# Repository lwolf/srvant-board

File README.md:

# srvant-board

| :warning: WARNING          |
|:---------------------------|
| This is a work-in-progress. No final board have been produced yet. Any part of the schematic and/or PCB could be wrong.|

Design of the carrier board for the Raspberry Pi CM4. The main distinction from existing boards is the presence of the 
BMC (Baseboard Management Controller) which supposed to monitor and control the HOST, allowing the board to act as a real "server".

## Highlevel design / idea:

BMC using lots of GPIO controls the HOST: power cycle, terminal access, switches USB into OTG for flushing.

* CM4 (HOST) features:
  * 1Gb/s ethernet
  * HDMI
  * 1 USB
  * PCIe exposed as M.2 socket to connect nvme drive
  * TPM2.0 (OPTIGA™ TPM SLB 9670)
  * RTC with battery
* BMC features:
  * Always ON
  * 1Gb/s management port
  * USB port for debug
  * USB connection to the HOST for flushing
  * I2C connection to the HOST for additional metrics
  * TTY connection to HOST for SOL (Serial over LAN)
  * measures Current/Power of the board
  * measures Temperature of the board
  * controls FAN (not available in the PoC)

BMC is based on the Allwinner T113 S3 SoM [link to aliexpress](https://www.aliexpress.com/item/1005005389129193.html).

### Power

THere are separate 5v rails for host and BMC. The host one is based on AP64501SP (5V 5A), while BMC is based on AP63205WU (5V 2A).
BMC is always on. Host is being powered either by a signal from BMC or by shortening a jumper.

Main power goes through the shunt resistor connected to the power sensor (INA219A). The value is available to BMC using i2c bus.

### Connectors

#### HOST
Host has a following connectors:
* Ethernet
* HDMI
* USB
* M.2 socket M for nvme disk

#### BMC
BMC has a following connectors:
* Ethernet (1GB/s)
* MicroUSB (debug)

### USB

There is a connection between BMC and HOST using USB to allow flushing the HOST remotely.
Since CM4 has only a single usb line, it is connected to the MUX (FSUSB42MUX) 
in a similar way it is done in the CM4IO board, but instead of switching client mode to microUSB, it goes to BMC.

### RTC

RTC is based on PCF85063AT chip. There are two of them, one for each CPU.
Even though t133-s3 has on-board RTC, it is not exposed from the SOM and reference schematic uses external one.
Both chips are powered by 3.3v coming from BMC and coin cell battery.

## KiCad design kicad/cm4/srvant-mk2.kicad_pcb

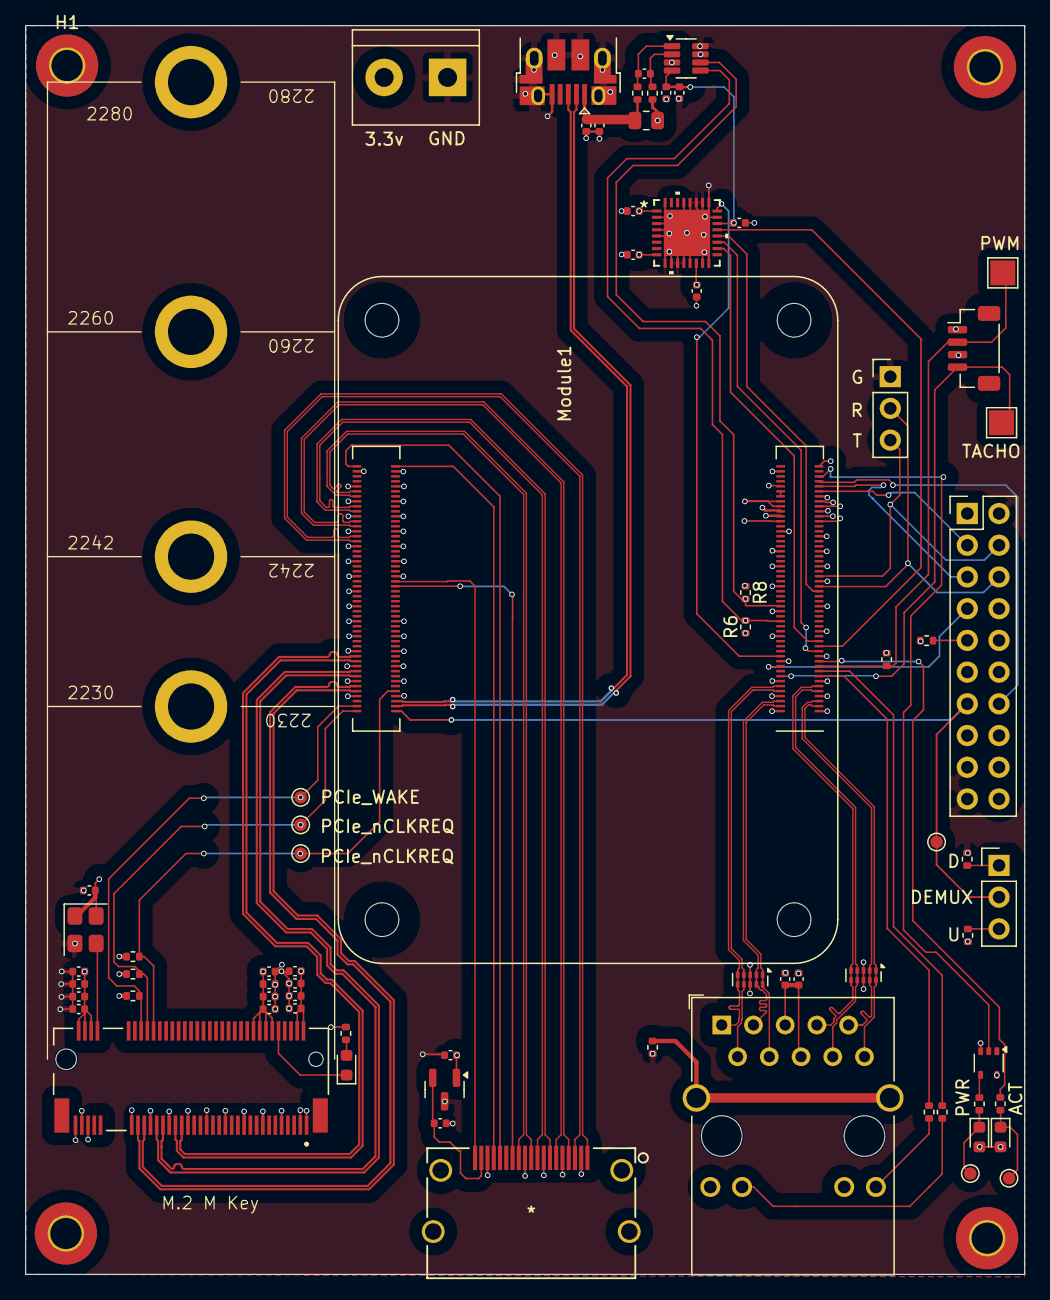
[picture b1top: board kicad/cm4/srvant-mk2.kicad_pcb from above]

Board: 6 copper layers, 80.0 x 100.0 mm, 76 parts (0 on the bottom side), 77 nets.

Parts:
C1, C2: 10uF; C_0402_1005Metric
C3, C5, C23, C25, C29, C30, C31, C42, C43, C44, C49, C50, C51: 100n; C_0402_1005Metric
C4, C35, C36, C37: 10u; C_0402_1005Metric
C28, C38, C39, C40: 1u; C_0402_1005Metric
C46, C47, C48: 1n; C_0402_1005Metric
D1: LED Green; LED_0603_1608Metric
D2: LED Red; LED_0603_1608Metric
D3: LED; LED_0603_1608Metric
FB1: 220R; R_0402_1005Metric
H1, H2, H3, H4: MountingHole; MountingHole_2.5mm_Pad_TopOnly
J1: Screw_Terminal_01x02; TerminalBlock_bornier-2_P5.08mm
J2: USB_B_Micro; USB_Micro-B_Amphenol_10103594-0001LF_Horizontal
J5, J6: Conn_01x03; PinHeader_1x03_P2.54mm_Vertical
J7: ARJM11; RJ45_Wuerth_7499111446_Horizontal
J8: Bus_M.2_Socket_M; M.2 M Key socket_rpi
J9: Conn_02x10_Odd_Even; PinHeader_2x10_P2.54mm_Vertical
J10: HDMI connector; HDMI-10029449-001RLF
J14: JST_SHBM04B-SRSS-TB; JST_SH_BM04B-SRSS-TB_1x04-1MP_P1.00mm_Vertical
Module1: ComputeModule5-CM5; Raspberry-Pi-4-Compute-Module
R1: 0.005R; R_0805_2012Metric
R2, R3: 10R; R_0402_1005Metric
R4: 1k; R_0402_1005Metric
R5, R6, R7, R8, R17, R18, R19, R20: 10K; R_0402_1005Metric
R13, R14: 470R; R_0402_1005Metric
R16: 1K; R_0402_1005Metric
R21: 330R; R_0402_1005Metric
R22: 10K 1%; R_0402_1005Metric
TP1, TP3: TestPoint; TestPoint_Pad_D1.0mm
TP4, TP11: PCIe_nCLKREQ; TestPoint_Pad_D1.0mm
TP5, TP8: PCIe_nRST; TestPoint_Pad_D1.0mm
TP9, TP10: TestPoint; TestPoint_Pad_2.0x2.0mm
U1: INA219AxDCN; SOT-23-8
U4, U5: TPD4EUSB30; USON-10_2.5x1.0mm_P0.5mm
U6: SLB9670VQ20FW785XTMA1; QFN32_SLB9670VQ20FW785XTMA1_INF
U8: 74LVC1G07SE-7; SOT-353_SC-70-5
U9: RT9742SNGV; SOT-23
U10: ASEK-32.768KHZ-L-R-T; Crystal_SMD_3225-4Pin_3.2x2.5mm

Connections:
/+1.8v: Module1.88 (+1.8v_(Output)), Module1.90 (+1.8v_(Output))
/+3.3v_HOST: C4.1, C5.1, C28.1, C29.2, C30.2, C31.2, D1.2 (A), D2.2 (A), J7.11 (LED2+), J7.13 (LED1+), Module1.78 (GPIO_VREF(1.8v/3.3v_Input)), Module1.84 (+3.3v_(Output)), Module1.86 (+3.3v_(Output)), R5.2, R6.1, R8.1, R20.2, R22.1, U1.4 (VS), U6.1 (NCI/VDD), U6.8 (VDD), U6.14 (NCI/VDD), U6.22 (VDD), U8.5 (VCC)
/+3v3_AUX: C35.1, C36.1, C37.1, C38.1, C39.1, C40.1, C42.1, C43.1, C44.1, C46.1, C47.1, C48.1, C51.1, J1.2, J8.2 (3.3V), J8.4 (3.3V), J8.12 (3.3V), J8.14 (3.3V), J8.16 (3.3V), J8.18 (3.3V), J8.70 (3.3V), J8.72 (3.3V), J8.74 (3.3V), R17.2, R18.2, R19.2, R21.1, U10.1 (EN), U10.4 (VDD)
/+5v_HOST: C49.1, J14.1, Module1.77 (+5v_(Input)), Module1.79 (+5v_(Input)), Module1.81 (+5v_(Input)), Module1.83 (+5v_(Input)), Module1.85 (+5v_(Input)), Module1.87 (+5v_(Input)), R1.1, R3.1, U9.1 (IN)
/+5v_HOST_HDMI: C50.1, J10.18 (+5V), U9.2 (OUT)
/+5v_IN: C1.1, C2.1, J2.1 (VBUS), R1.2, R2.1
/BMC_HOST_BT_nDis: J9.5, Module1.91 (BT_nDisable)
/BMC_HOST_EEPROM_nWP: J9.7, Module1.20 (EEPROM_nWP)
/BMC_HOST_I2C_SCK: J9.10, Module1.80 (SCL0)
/BMC_HOST_I2C_SDA: J9.8, Module1.82 (SDA0)
/BMC_HOST_POST_COMPLETE: J9.9, R20.1
/BMC_HOST_POWER_OUT: J9.16, Module1.92 (PWR_BUT)
/BMC_HOST_RESET_OUT: J9.15, Module1.99 (PMIC_ENABLE)
/BMC_HOST_UART_RX: J6.2, J9.6, Module1.51 (GPIO15)
/BMC_HOST_UART_TX: J6.3, J9.4, Module1.55 (GPIO14)
/BMC_HOST_USB_DEMUX_CONTROL: J5.2, J9.13, Module1.101 (USB_OTG_ID), TP8.1
/BMC_HOST_WL_nDis: J9.3, Module1.89 (WiFi_nDisable)
/BMC_HOST_nRPIBOOT: J9.14, Module1.93 (nRPIBOOT)
/ETH_LEDG: Module1.17 (Ethernet_nLED2(3.3v)), R13.2
/ETH_LEDY: Module1.15 (Ethernet_nLED3(3.3v)), R14.2
/GPIO10: J9.20, Module1.44 (GPIO10), R8.2, U1.6 (SDA)
/GPIO11: J9.18, Module1.38 (GPIO11), R6.2, U1.5 (SCL)
/GPIO16: Module1.29 (GPIO16), U6.18 (PIRQ#)
/GPIO18: Module1.49 (GPIO18), U6.20 (CS#)
/GPIO20: Module1.27 (GPIO20), U6.21 (MOSI)
/GPIO21: Module1.25 (GPIO21), U6.19 (SCLK)
/HDMI0_CEC: J10.13 (CEC), Module1.151 (HDMI0_CEC)
/HDMI0_CK_N: J10.12 (CK-), Module1.190 (HDMI0_CLK_N)
/HDMI0_CK_P: J10.10 (CK+), Module1.188 (HDMI0_CLK_P)
/HDMI0_D0_N: J10.9 (D0-), Module1.184 (HDMI0_TX0_N)
/HDMI0_D0_P: J10.7 (D0+), Module1.182 (HDMI0_TX0_P)
/HDMI0_D1_N: J10.6 (D1-), Module1.178 (HDMI0_TX1_N)
/HDMI0_D1_P: J10.4 (D1+), Module1.176 (HDMI0_TX1_P)
/HDMI0_D2_N: J10.3 (D2-), Module1.172 (HDMI0_TX2_N)
/HDMI0_D2_P: J10.1 (D2+), Module1.170 (HDMI0_TX2_P)
/HDMI0_HOTPLUG: J10.19 (HPD/HEAC-), Module1.153 (HDMI0_HOTPLUG)
/HDMI0_SCL: J10.15 (SCL), Module1.200 (HDMI0_SCL)
/HDMI0_SDA: J10.16 (SDA), Module1.199 (HDMI0_SDA)
/HOST_SPI1_MISO: Module1.24 (GPIO26), U6.24 (MISO)
/PCIE_CLK_N: J8.53 (REFCLKn), Module1.112 (PCIe_CLK_N)
/PCIE_CLK_P: J8.55 (REFCLKp), Module1.110 (PCIe_CLK_P)
/PCIE_CLK_nREQ: J8.52 (~CLKREQ), Module1.102 (PCIe_nCLKREQ), R18.1, TP5.1
/PCIE_RX_N: J8.47 (PETn0/SATA-A-), Module1.118 (PCIe_RX_N)
/PCIE_RX_P: J8.49 (PETp0/SATA-A+), Module1.116 (PCIe_RX_P)
/PCIE_TX_N: J8.41 (PERn0/SATA-B+), Module1.124 (PCIe_TX_N)
/PCIE_TX_P: J8.43 (PERp0/SATA-B-), Module1.122 (PCIe_TX_P)
/PCIE_WAKE: J8.54 (~PEWAKE), Module1.104 (PCIE_nWAKE), R19.1, TP11.1
/PCIE_nRST: J8.50 (~PERST), Module1.109 (PCIe_nRST), R17.1, TP4.1
/PWM: J14.2, Module1.19 (FAN_PWM), R22.2, TP9.1
/TACHO: J14.4, Module1.16 (FAN_TACHO), TP10.1
/TRD0_N: J7.2 (TD1-), Module1.10 (Ethernet_Pair0_N), U5.4 (D2+), U5.7
/TRD0_P: J7.1 (TD1+), Module1.12 (Ethernet_Pair0_P), U5.5 (D2-), U5.6
/TRD1_N: J7.3 (TD2+), Module1.6 (Ethernet_Pair1_N), U5.2 (D1-), U5.9
/TRD1_P: J7.4 (TD2-), Module1.4 (Ethernet_Pair1_P), U5.1 (D1+), U5.10
/TRD2_N: J7.8 (TD3-), Module1.9 (Ethernet_Pair2_N), U4.4 (D2+), U4.7
/TRD2_P: J7.7 (TD3+), Module1.11 (Ethernet_Pair2_P), U4.5 (D2-), U4.6
/TRD3_N: J7.9 (TD4+), Module1.5 (Ethernet_Pair3_N), U4.2 (D1-), U4.9
/TRD3_P: J7.10 (TD4-), Module1.3 (Ethernet_Pair3_P), U4.1 (D1+), U4.10
/USB2_N: J2.2 (D-), Module1.103 (USB2_N)
/USB2_P: J2.3 (D+), Module1.105 (USB2_P)
/nPWR_LED: Module1.95 (LED_nPWR), U8.2
GND: C1.2, C2.2, C4.2, C5.2, C23.2, C25.2, C28.2, C29.1, C30.1, C31.1, C35.2, C36.2, C37.2, C38.2, C39.2, C40.2, C42.2, C43.2, C44.2, C46.2, C47.2, C48.2, C49.2, C50.2, C51.2, FB1.2, J1.1, J2.5 (GND), J2.6 (Shield), J6.1, J8.1 (GND), J8.3 (GND), J8.9 (GND), J8.15 (GND), J8.21 (GND), J8.27 (GND), J8.33 (GND), J8.39 (GND), J8.45 (GND), J8.51 (GND), J8.57 (GND), J8.71 (GND), J8.73 (GND), J8.75 (GND), J9.2, J9.11, J9.12, J9.17, J9.19, J10.2 (D2S), J10.5 (D1S), J10.8 (D0S), J10.11 (CKS), J10.17 (GND), J14.3, Module1.1 (GND), Module1.2 (GND), Module1.7 (GND), Module1.8 (GND), Module1.13 (GND), Module1.14 (GND), Module1.22 (GND), Module1.23 (GND), Module1.32 (GND), Module1.33 (GND), Module1.42 (GND), Module1.43 (GND), Module1.52 (GND), Module1.53 (GND), Module1.59 (GND), Module1.60 (GND), Module1.65 (GND), Module1.66 (GND), Module1.71 (GND), Module1.74 (GND), Module1.98 (GND), Module1.107 (GND), Module1.108 (GND), Module1.113 (GND), Module1.114 (GND), Module1.119 (GND), Module1.120 (GND), Module1.125 (GND), Module1.126 (GND), Module1.131 (GND), Module1.132 (GND), Module1.137 (GND), Module1.138 (GND), Module1.144 (GND), Module1.150 (GND), Module1.155 (GND), Module1.156 (GND), Module1.161 (GND), Module1.162 (GND), Module1.167 (GND), Module1.168 (GND), Module1.173 (GND), Module1.174 (GND), Module1.179 (GND), Module1.180 (GND), Module1.185 (GND), Module1.186 (GND), Module1.191 (GND), Module1.192 (GND), Module1.197 (GND), Module1.198 (GND), R7.1, U1.3 (GND), U1.7 (A0), U1.8 (A1), U4.3 (GND), U4.8 (GND), U5.3 (GND), U5.8 (GND), U6.2 (GND), U6.3 (NCI), U6.4 (NCI), U6.5 (NCI), U6.9 (GND), U6.10 (NCI), U6.11 (NCI), U6.12 (NCI), U6.13 (NCI), U6.15 (NCI), U6.16 (NCI/GND), U6.23 (GND), U6.25 (NCI), U6.26 (NCI), U6.27 (NCI), U6.28 (NCI), U6.29 (NCI), U6.32 (NCI), U6.33 (GND), U8.3 (GND), U9.3 (GND), U10.2 (GND)
unnamed: C23.1, C25.1, J7.5 (CT), J7.6 (CT)
unnamed: D1.1 (K), R4.1, TP1.1
unnamed: D2.1 (K), R16.1, TP3.1
unnamed: D3.2 (A), R21.2
unnamed: D3.1 (K), J8.10 (DAS/~DSS/~LED1)
unnamed: FB1.1, J7.SH
unnamed: J5.1, R7.2
unnamed: J5.3, R5.1
unnamed: J7.14 (LED1-), R14.1
unnamed: J7.12 (LED2-), R13.1
unnamed: J8.68 (SUSCLK), U10.3 (Out)
unnamed: Module1.21 (LED_nACT), R4.2
unnamed: R16.2, U8.4
unnamed: C3.1, R2.2, U1.1 (IN+)
unnamed: C3.2, R3.2, U1.2 (IN-)

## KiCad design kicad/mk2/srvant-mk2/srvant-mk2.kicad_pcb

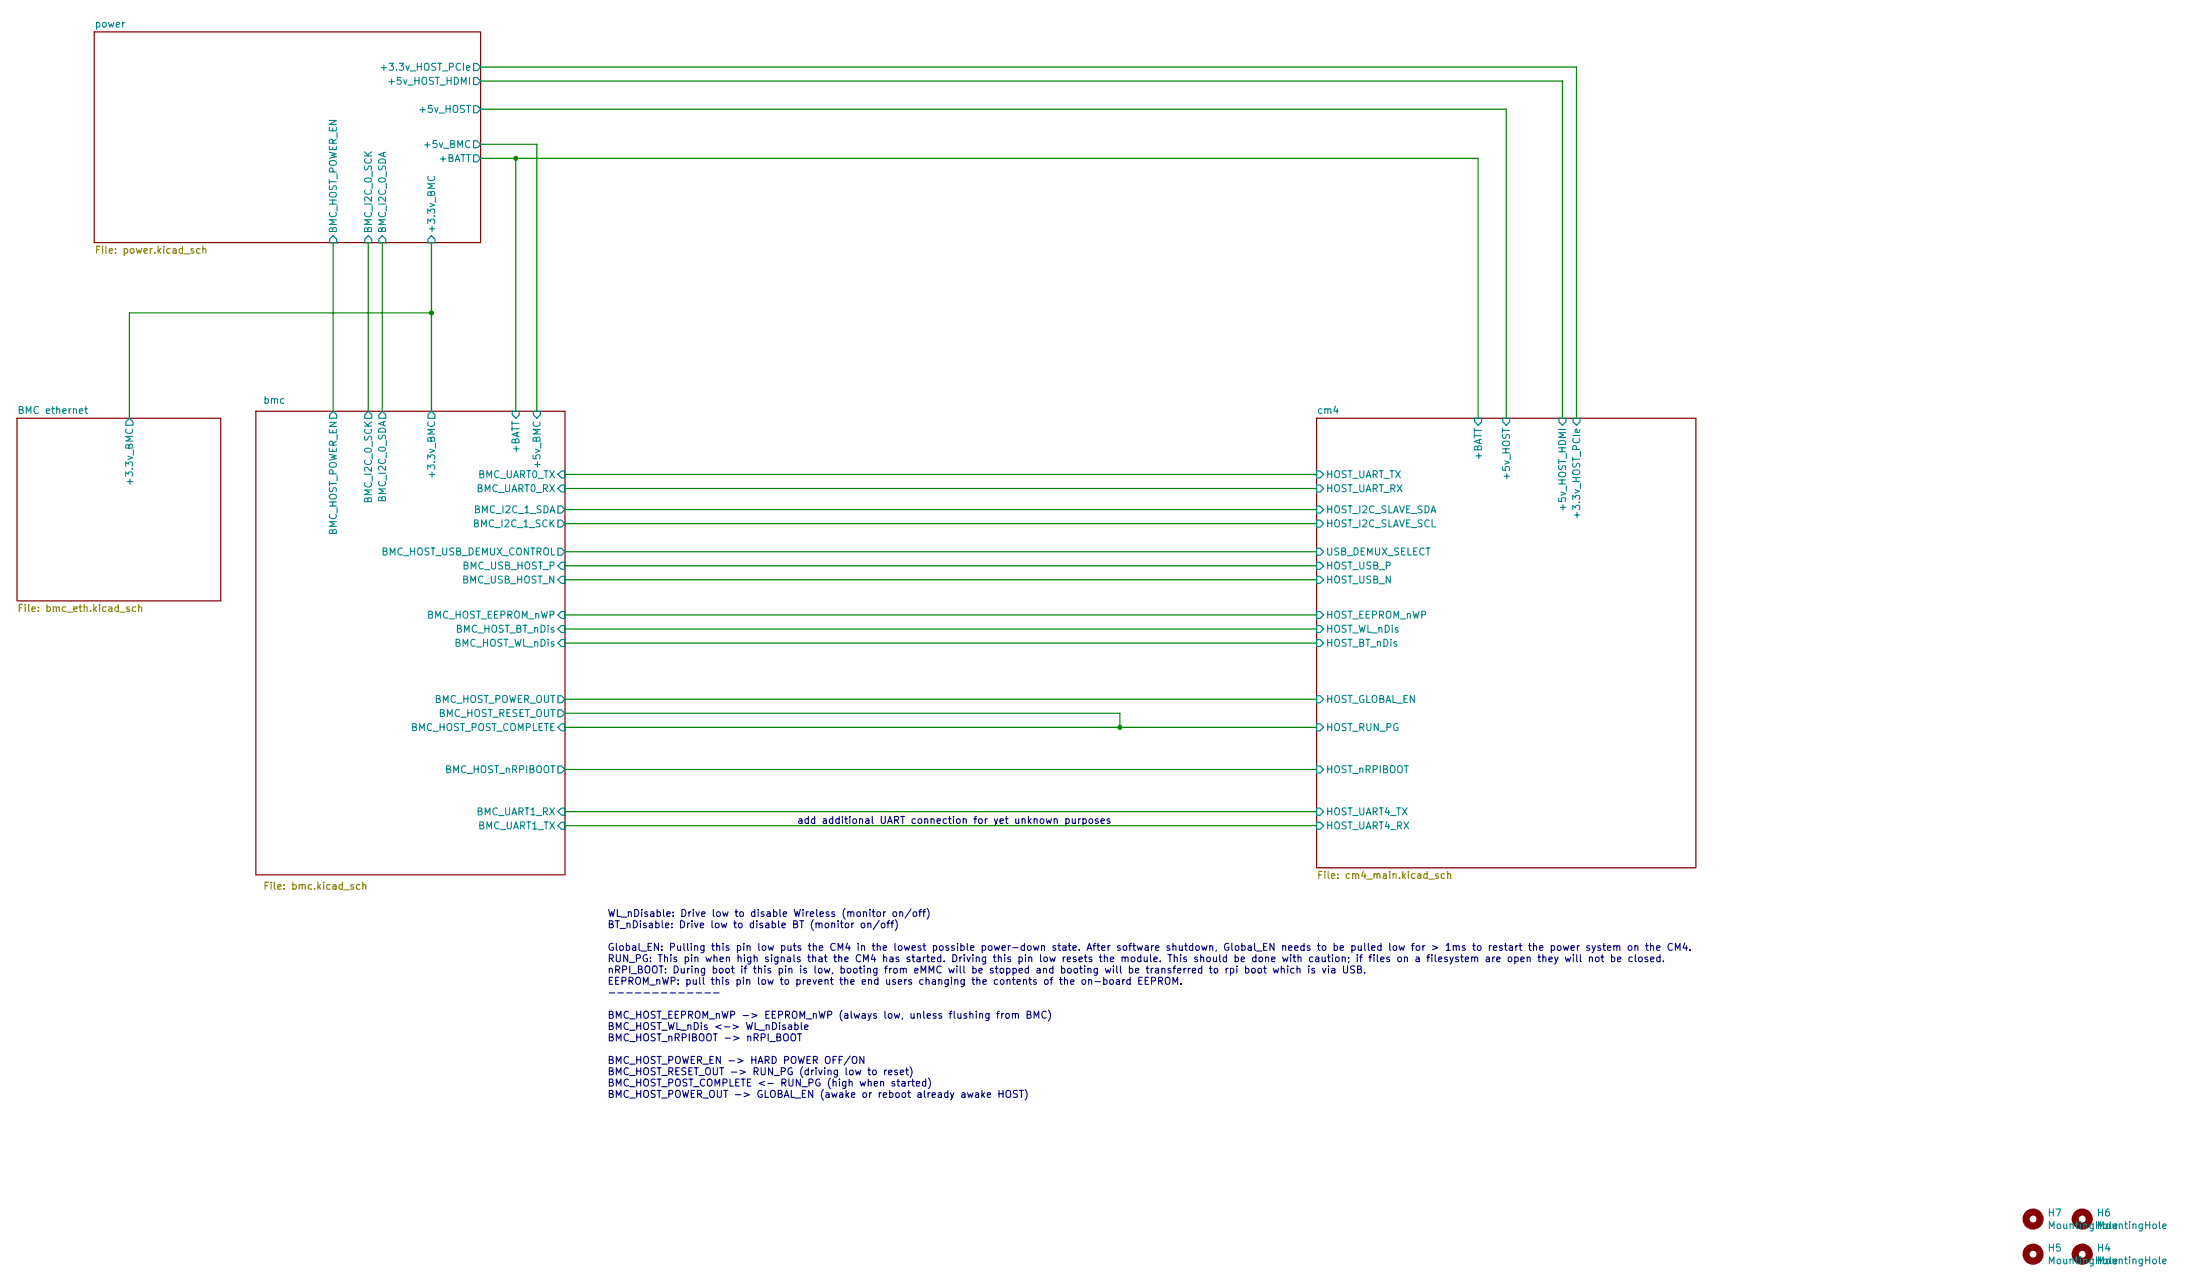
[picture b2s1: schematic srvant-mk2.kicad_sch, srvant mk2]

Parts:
H4, H5, H6, H7: MountingHole; MountingHole_2.5mm_Pad_TopOnly; Part Description M2.5 mounting hole

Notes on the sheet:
WL_nDisable: Drive low to disable Wireless (monitor on/off) BT_nDisable: Drive low to disable BT (monitor on/off) Global_EN: Pulling this pin low puts the CM4 in the lowest possible power-down state. After software shutdown, Global_EN needs to be pulled low for > 1ms to restart the power system on 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
add additional UART connection for yet unknown purposes

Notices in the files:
parts and their libraries:
Copyright 2016 Accelerated Designs. All rights reserved.
